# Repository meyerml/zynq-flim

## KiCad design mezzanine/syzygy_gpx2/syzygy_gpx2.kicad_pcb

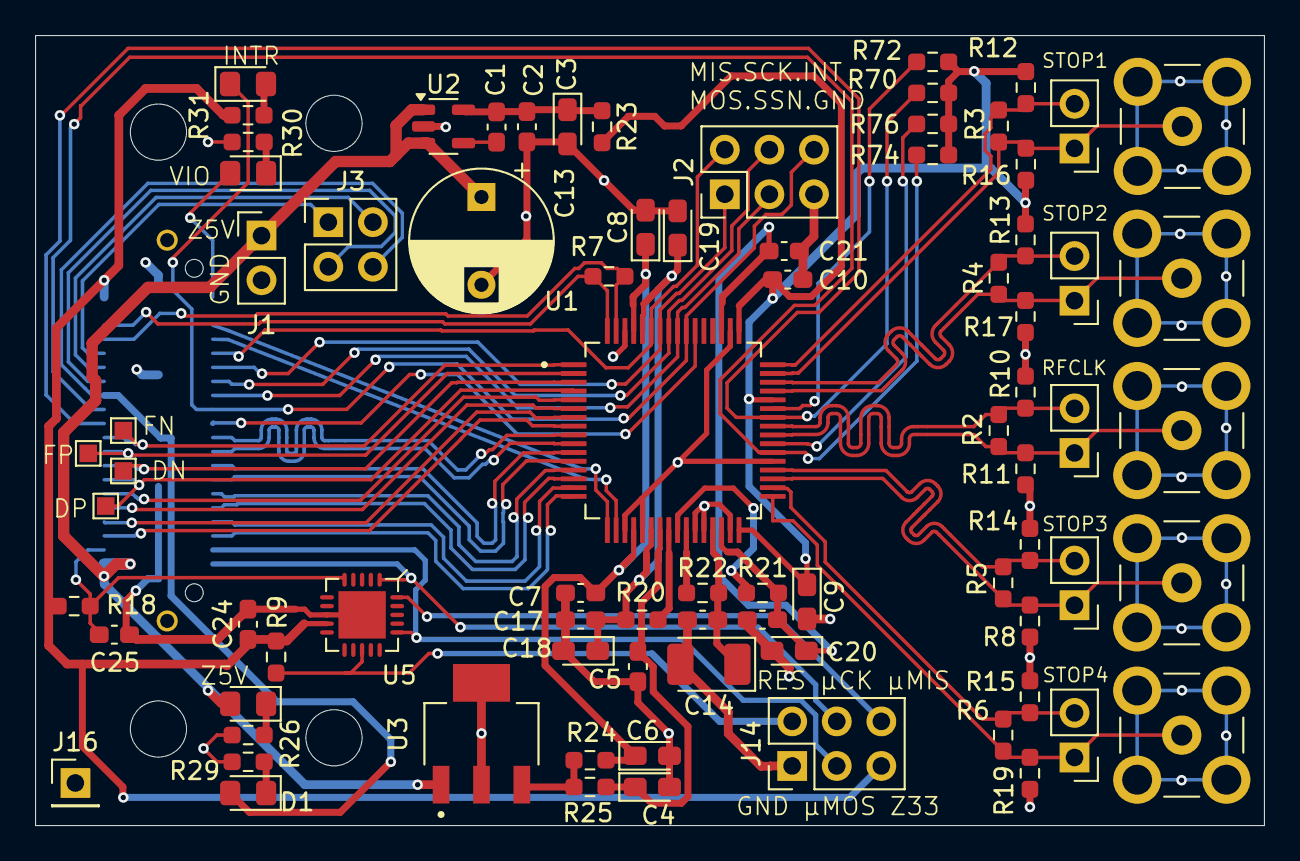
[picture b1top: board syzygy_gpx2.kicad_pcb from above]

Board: 4 copper layers, 70.0 x 45.0 mm, 85 parts (1 on the bottom side), 69 nets.

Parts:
C1: 1n; C_0603_1608Metric_Pad1.08x0.95mm_HandSolder
C2, C5, C7, C10, C15, C16, C17, C21: 100n; C_0603_1608Metric_Pad1.08x0.95mm_HandSolder
C3, C20: 100u; CP_EIA-2012-15_AVX-P_Pad1.30x1.05mm_HandSolder
C4, C6, C8, C9, C18, C19: 33u; CP_EIA-2012-15_AVX-P_Pad1.30x1.05mm_HandSolder
C13: 330u; CP_Radial_D8.0mm_P5.00mm
C14: 220u; CP_EIA-3528-21_Kemet-B_Pad1.50x2.35mm_HandSolder
C24: 0.1uF; C_0603_1608Metric_Pad1.08x0.95mm_HandSolder
C25: 0.1uF DNP; C_0603_1608Metric_Pad1.08x0.95mm_HandSolder
D1, D2, D3, D4: LED; LED_0805_2012Metric_Pad1.15x1.40mm_HandSolder
DN1: TestPoint_Probe; TestPoint_Pad_1.0x1.0mm
DP1: TestPoint_Probe; TestPoint_Pad_1.0x1.0mm
FN1: TestPoint_Probe; TestPoint_Pad_1.0x1.0mm
FP1: TestPoint_Probe; TestPoint_Pad_1.0x1.0mm
H1, H2, H3, H4: MountingHole; MountingHole_3.2mm_M3_DIN965
J1, J4, J5, J6, J7, J8: Conn_01x02; PinHeader_1x02_P2.54mm_Vertical
J2: Conn_02x03_Counter_Clockwise; PinHeader_2x03_P2.54mm_Vertical
J3: Conn_01x04; PinHeader_2x02_P2.54mm_Vertical
J9, J10, J11, J12, J13: Conn_Coaxial; SMB_Jack_Vertical_mod
J14: Conn_02x03_Odd_Even; PinHeader_2x03_P2.54mm_Vertical
J15: SYZYGY_STD; QTE-020-01-F-D-A
J16: Conn_01x01; PinHeader_1x01_P2.54mm_Vertical
R2, R3, R4, R5, R6, R7: 100; R_0603_1608Metric_Pad0.98x0.95mm_HandSolder
R8, R10, R11, R12, R13, R14, R15, R16, R17, R19, R70, R72, R74, R76: 100k; R_0603_1608Metric_Pad0.98x0.95mm_HandSolder
R9, R18: 10K; R_0603_1608Metric_Pad0.98x0.95mm_HandSolder
R20, R21, R22, R23, R24, R25: 0; R_0603_1608Metric_Pad0.98x0.95mm_HandSolder
R26, R31: 330; R_0603_1608Metric_Pad0.98x0.95mm_HandSolder
R29, R30: 75; R_0603_1608Metric_Pad0.98x0.95mm_HandSolder
U1: TDC-GPX2_FLQM; QFP50P1200X1200X160-64N
U2: LT1761-3.3; TSOT-23-5
U3: LM3940IMPX-3.3_NOPB; SOT230P700X180-4N
U5: ATtiny44A-MU; QFN-24-4x4mm

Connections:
/Inputs/REFCLKN: J4.2, R2.2, R10.1, U1.41 (REFCLKN)
/Inputs/REFCLKP: J4.1, J9.1 (In), R2.1, R11.1, U1.40 (REFCLKP)
/Inputs/STOP1N: J5.2, R3.2, R12.1, U1.48 (STOP1N)
/Inputs/STOP1P: J5.1, J10.1 (In), R3.1, R16.1, U1.47 (STOP1P)
/Inputs/STOP2N: J6.2, R4.2, R13.1, U1.46 (STOP2N)
/Inputs/STOP2P: J6.1, J11.1 (In), R4.1, R17.1, U1.45 (STOP2P)
/Inputs/STOP3N: J7.2, R5.2, R14.1, U1.36 (STOP3N)
/Inputs/STOP3P: J7.1, J12.1 (In), R5.1, R8.1, U1.35 (STOP3P)
/Inputs/STOP4N: J8.2, R6.2, R15.1, U1.34 (STOP4N)
/Inputs/STOP4P: J8.1, J13.1 (In), R6.1, R19.1, U1.33 (STOP4P)
/Power/DVDD33O: R24.1, R25.1, U3.3 (OUT)
/Power/TVDD33O: C1.2, C2.1, C3.1, R23.1, U2.5 (VOUT)
/SYZYGY/DISABLEP: J15.24 (S19), R74.1, U1.38 (DISABLEP)
/SYZYGY/FRAME1N: FN1.1, J15.20 (S15_D7N), U1.1 (FRAME1N)
/SYZYGY/FRAME1P: FP1.1, J15.18 (S13_D7P), U1.2 (FRAME1P)
/SYZYGY/FRAME2N: J15.12 (S7_D3N), U1.5 (FRAME2N)
/SYZYGY/FRAME2P: J15.10 (S5_D3P), U1.6 (FRAME2P)
/SYZYGY/FRAME3N: J15.19 (S14_D6N), U1.9 (FRAME3N)
/SYZYGY/FRAME3P: J15.17 (S12_D6P), U1.10 (FRAME3P)
/SYZYGY/FRAME4N: J15.11 (S6_D2N), U1.13 (FRAME4N)
/SYZYGY/FRAME4P: J15.9 (S4_D2P), U1.14 (FRAME4P)
/SYZYGY/INTERRUPT_N: D4.1 (K), J2.6, J15.23 (S18), U1.55 (~INTERRUPT)
/SYZYGY/LCLKINN: J15.36 (C2P_CLKn), R7.2, U1.64 (LCLKINN)
/SYZYGY/LCLKINP: J15.34 (C2P_CLKp), R7.1, U1.63 (LCLKINP)
/SYZYGY/LCLKOUTN: J15.35 (P2C_CLKn), U1.17 (LCLKOUTN)
/SYZYGY/LCLKOUTP: J15.33 (P2C_CLKp), U1.18 (LCLKOUTP)
/SYZYGY/MCU_MISO: J14.6, U5.20 (PA5)
/SYZYGY/MCU_RESET_B: J14.2, R9.2, U5.13 (~RESET/PB3)
/SYZYGY/MCU_SCL_USCK: J14.4, J15.1 (SCL), U5.1 (PA4)
/SYZYGY/MCU_SDA_MOSI: J14.3, J15.3 (SDA), U5.16 (PA6)
/SYZYGY/MISO: J2.2, J15.31 (S26), U1.59 (MISO)
/SYZYGY/MOSI: J2.1, J15.29 (S24), U1.58 (MOSI)
/SYZYGY/PARITY: J15.21 (S16), U1.54 (PARITY)
/SYZYGY/REFRESP: J15.22 (S17), R70.1, U1.42 (RSTIDXP)
/SYZYGY/R_GA: C25.1, J15.4 (R_GA), R18.2, U5.5 (AREF/PA0)
/SYZYGY/SCK: J2.4, J15.27 (S22), U1.57 (SCK)
/SYZYGY/SDO1N: DN1.1, J15.16 (S11_D5N), U1.3 (SDO1N)
/SYZYGY/SDO1P: DP1.1, J15.14 (S9_D5P), U1.4 (SDO1P)
/SYZYGY/SDO2N: J15.8 (S3_D1N), U1.7 (SDO2N)
/SYZYGY/SDO2P: J15.6 (S1_D1P), U1.8 (SDO2P)
/SYZYGY/SDO3N: J15.15 (S10_D4N), U1.11 (SDO3N)
/SYZYGY/SDO3P: J15.13 (S8_D4P), U1.12 (SDO3P)
/SYZYGY/SDO4N: J15.7 (S2_D0N), U1.15 (SDO4N)
/SYZYGY/SDO4P: J15.5 (S0_D0P), U1.16 (SDO4P)
/SYZYGY/SS_N: J2.3, J15.25 (S20), U1.56 (~SSN)
/SYZYGY/VIO: D3.2 (A), J15.39 (VIO)
/gpx2/CVDD18: C14.1, C15.1, R22.2, U1.29 (CVDD18)
/gpx2/CVDD18O: R22.1, U1.26 (CVDD18O)
/gpx2/DVDD18: C17.1, C18.1, C19.1, R20.2, U1.22 (DVDD18), U1.60 (DVDD18__1)
/gpx2/DVDD18O: R20.1, U1.24 (DVDD18O)
/gpx2/TVDD18: C16.1, C20.1, C21.1, R21.2, U1.30 (TVDD18), U1.51 (TVDD18__1)
/gpx2/TVDD18O: R21.1, U1.25 (TVDD18O)
DVDD33: C6.1, C7.1, C8.1, R24.2, U1.20 (DVDD33), U1.61 (DVDD33__1)
GND: C2.2, C3.2, C4.2, C5.2, C6.2, C7.2, C8.2, C9.2, C10.2, C13.2, C14.2, C15.2, C16.2, C17.2, C18.2, C19.2, C20.2, C21.2, C24.2, C25.2, J1.2, J2.5, J9.2 (Ext), J10.2 (Ext), J11.2 (Ext), J12.2 (Ext), J13.2 (Ext), J14.1, J15.0 (GND), J16.1, R26.2, R29.2, R30.2, U1.19 (DGND), U1.21 (DGND__1), U1.27 (RGND), U1.28 (CGND), U1.31 (TGND), U1.37 (TGND__1), U1.50 (TGND__2), U1.62 (DGND__2), U2.2 (GND), U3.2 (GND), U3.4 (GND), U5.8 (GND), U5.21 (GND)
unnamed: D1.2 (A), J3.4, J15.26 (S21)
unnamed: D1.1 (K), R29.1
unnamed: D2.1 (K), R26.1
unnamed: D3.1 (K), R30.1
unnamed: D4.2 (A), R31.2
unnamed: J3.3, J15.28 (S23)
unnamed: J3.2, J15.30 (S25)
unnamed: J3.1, J15.32 (S27)
unnamed: R76.1, U1.39 (DISABLEN)
unnamed: R72.1, U1.43 (RSTIDXN)
unnamed: C1.1, U2.4 (BYP)
RVDD33: C4.1, C5.1, R25.2, U1.23 (RVDD33)
SZG5V: C13.1, D2.2 (A), J1.1, J15.2 (5V), U2.1 (VIN), U2.3 (~SHDN), U3.1 (IN)
SZG33: C24.1, J14.5, J15.40 (+3.3V), R9.1, R18.1, R31.1, U5.9 (VCC)
TVDD33: C9.1, C10.1, R8.2, R10.2, R11.2, R12.2, R13.2, R14.2, R15.2, R16.2, R17.2, R19.2, R23.2, R70.2, R72.2, R74.2, R76.2, U1.32 (TVDD33), U1.44 (TVDD33__1), U1.49 (TVDD33__2)

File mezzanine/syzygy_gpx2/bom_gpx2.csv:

"Reference";"Value";"Datasheet";"Footprint";"Qty";"DNP"
"C1";"1n";"~";"Capacitor_SMD:C_0603_1608Metric_Pad1.08x0.95mm_HandSolder";"1";""
"C2,C5,C7,C10,C15,C16,C17,C21";"100n";"~";"Capacitor_SMD:C_0603_1608Metric_Pad1.08x0.95mm_HandSolder";"8";""
"C3,C20";"100u";"-- mixed values --";"Capacitor_Tantalum_SMD:CP_EIA-2012-15_AVX-P_Pad1.30x1.05mm_HandSolder";"2";""
"C4,C6,C8,C9,C18,C19";"33u";"-- mixed values --";"Capacitor_Tantalum_SMD:CP_EIA-2012-15_AVX-P_Pad1.30x1.05mm_HandSolder";"6";""
"C13";"330u";"~";"Capacitor_THT:CP_Radial_D8.0mm_P5.00mm";"1";""
"C14";"220u";"~";"Capacitor_Tantalum_SMD:CP_EIA-3528-21_Kemet-B_Pad1.50x2.35mm_HandSolder";"1";""
"C24";"0.1uF";"~";"Capacitor_SMD:C_0603_1608Metric_Pad1.08x0.95mm_HandSolder";"1";""
"J1";"Conn_01x02";"~";"Connector_PinHeader_2.54mm:PinHeader_1x02_P2.54mm_Vertical";"1";""
"J2";"Conn_02x03_Counter_Clockwise";"~";"Connector_PinHeader_2.54mm:PinHeader_2x03_P2.54mm_Vertical";"1";""
"J9,J10,J11,J12,J13";"Conn_Coaxial";"~";"Marcel:SMB_Jack_Vertical_mod";"5";""
"J14";"Conn_01x06";"~";"Connector_PinHeader_2.54mm:PinHeader_1x06_P2.54mm_Vertical";"1";""
"J15";"SYZYGY_STD";"http://suddendocs.samtec.com/catalog_english/qte.pdf";"SYZYGY:QTE-020-01-F-D-A";"1";""
"R7";"100";"~";"Resistor_SMD:R_0603_1608Metric_Pad0.98x0.95mm_HandSolder";"1";""
"R8,R10,R11,R12,R13,R14,R15,R16,R17,R19,R70,R72,R74,R76";"100k";"~";"Resistor_SMD:R_0603_1608Metric_Pad0.98x0.95mm_HandSolder";"14";""
"R9,R18";"10K";"~";"Resistor_SMD:R_0603_1608Metric_Pad0.98x0.95mm_HandSolder";"2";""
"R20,R21,R22,R23,R24,R25";"0";"~";"Resistor_SMD:R_0603_1608Metric_Pad0.98x0.95mm_HandSolder";"6";""
"U1";"TDC-GPX2_FLQM";"";"TDC_GPX2_FLQM:QFP50P1200X1200X160-64N";"1";""
"U2";"LT1761-3.3";"https://www.analog.com/media/en/technical-documentation/data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";"Package_TO_SOT_SMD:TSOT-23-5";"1";""
"U3";"LM3940IMPX-3.3_NOPB";"";"LM3940IMPX-3.3_NOPB:SOT230P700X180-4N";"1";""
"U5";"ATtiny44A-MU";"http://ww1.microchip.com/downloads/en/DeviceDoc/doc8183.pdf";"SYZYGY:QFN-24-4x4mm";"1";""

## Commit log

2025-04-24 upload two vivado projects
2025-04-28 vitis project
2025-04-28 init should work
2025-04-28 data readout comiles
2025-05-05 spi_to_dma working
2025-05-15 save progress
2025-05-23 working dma transfer via spi
2025-06-02 added kicad files for test
2025-06-30 starting work on zedboard soon
2025-07-30 custom board hard-and software added
2025-07-30 added the spi module
2025-08-22 single_channel_LVDS working
2025-09-02 before vacation, reporting per pixel works
2025-09-02 after vac
2025-10-15 DDRLVDS
2025-10-15 the module of the DDRLVDS
2025-10-25 working and meeting static timing after synthesis
2025-10-27 workinggit stage DDR_LVDS_FABRIC!
2025-11-20 backup before ssd change
2025-12-03 save new hist method before laptop dies
2025-12-03 also the old version whcih was working
2025-12-03 signal generator
2026-01-08 signal generator and DMA working with hist method
2026-02-24 python scripts
2026-02-24 histogram module
2026-02-24 laser_emulator
2026-02-24 LVDS_to_AXIS
2026-02-24 vitis_histogram
2026-02-24 signal_generator
